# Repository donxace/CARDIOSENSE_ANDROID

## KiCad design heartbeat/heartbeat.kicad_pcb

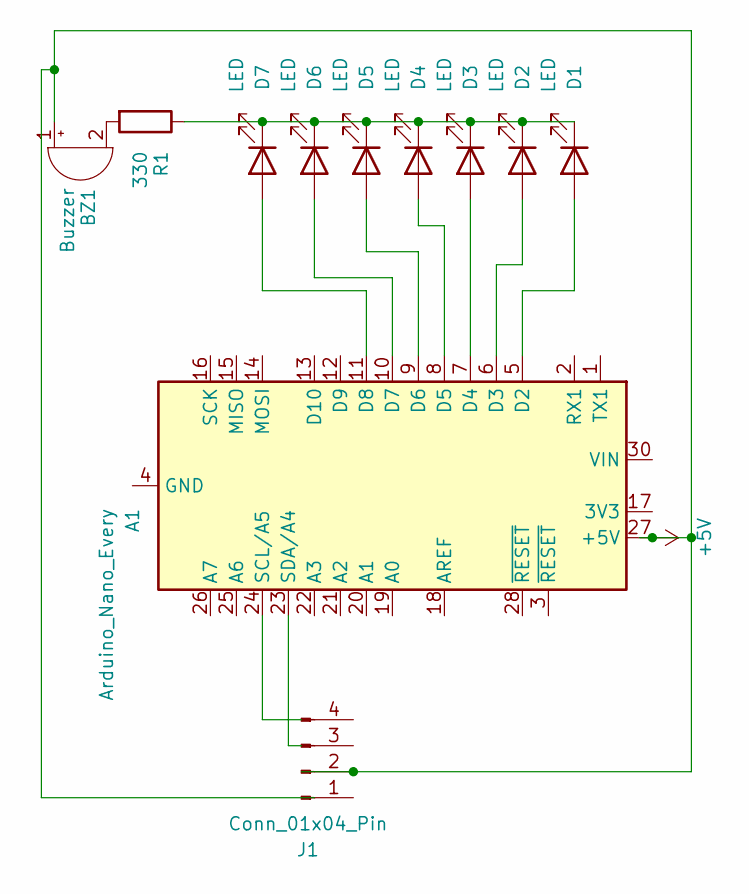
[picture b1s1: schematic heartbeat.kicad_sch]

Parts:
A1: Arduino_Nano_Every; Arduino_Nano
BZ1: Buzzer; Buzzer_15x7.5RM7.6
D1, D2, D3, D4, D5, D6, D7: LED; LED_D3.0mm
J1: Conn_01x04_Pin; PinHeader_1x04_P2.54mm_Vertical
R1: 330; R_Axial_DIN0207_L6.3mm_D2.5mm_P10.16mm_Horizontal

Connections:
+5V: A1.27 (+5V), BZ1.1 (+), J1.2
unnamed: A1.5 (D2), D1.2 (A)
unnamed: A1.6 (D3), D2.2 (A)
unnamed: A1.7 (D4), D3.2 (A)
unnamed: A1.8 (D5), D4.2 (A)
unnamed: A1.9 (D6), D5.2 (A)
unnamed: A1.10 (D7), D6.2 (A)
unnamed: A1.11 (D8), D7.2 (A)
unnamed: A1.4 (GND), A1.29 (GND)
unnamed: BZ1.2 (-), R1.2
unnamed: D1.1 (K), D2.1 (K), D3.1 (K), D4.1 (K), D5.1 (K), D6.1 (K), D7.1 (K), R1.1

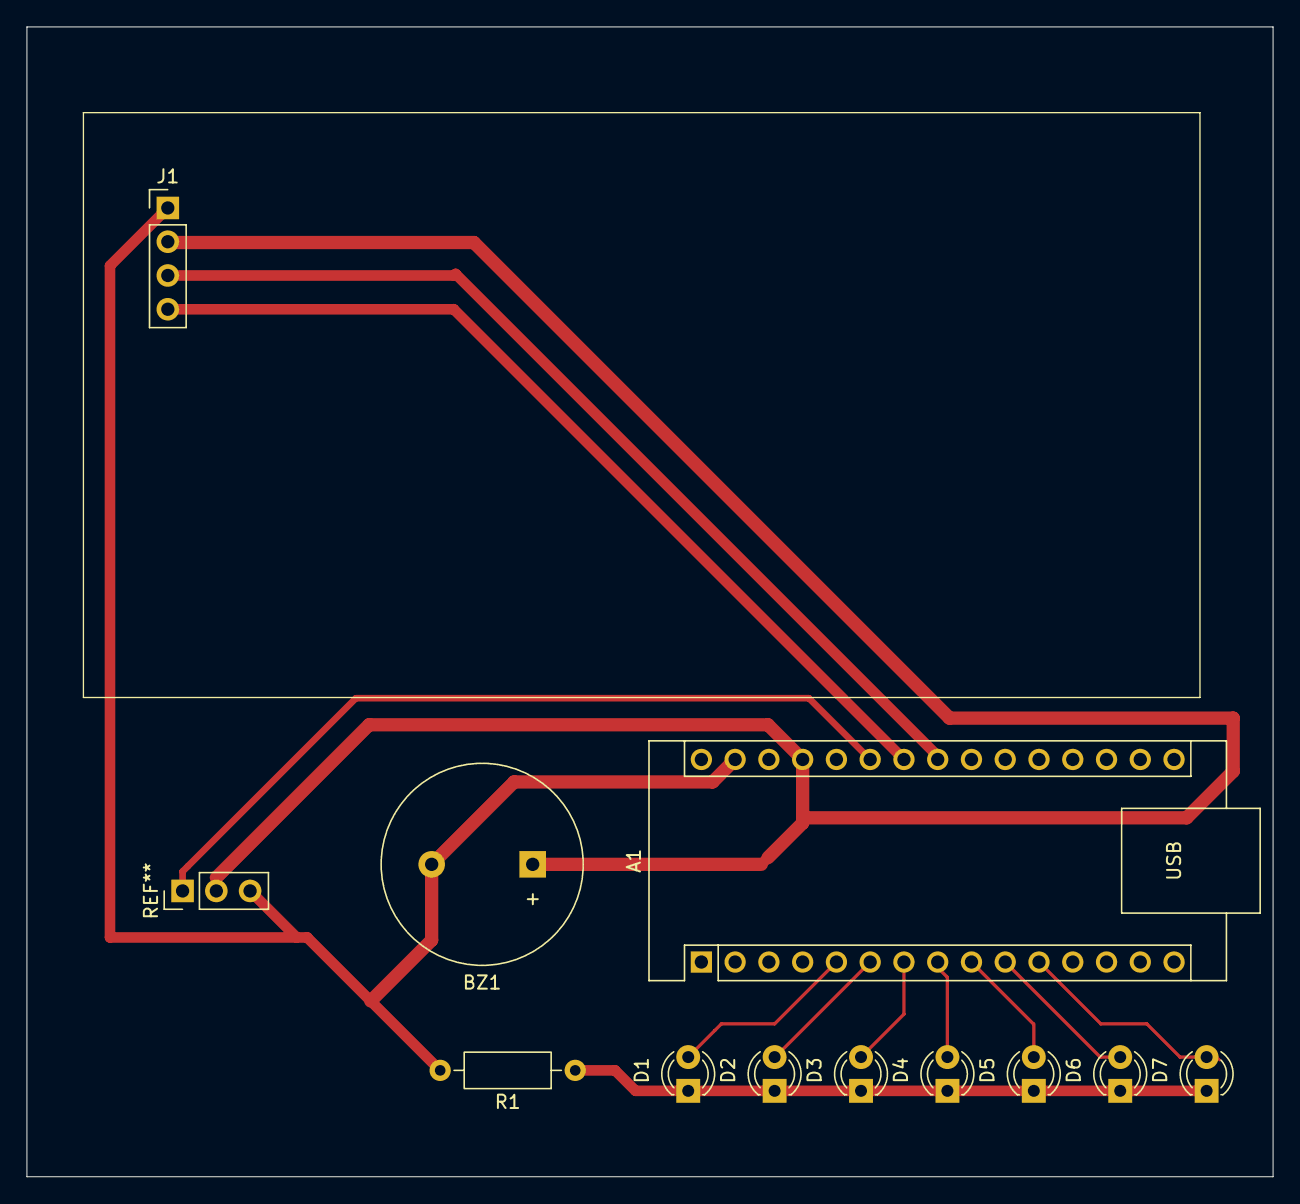
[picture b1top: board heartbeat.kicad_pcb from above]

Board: 2 copper layers, 93.8 x 86.5 mm, 11 parts (0 on the bottom side), 11 nets.

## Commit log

2025-11-06 Add SQLite Table for LSTM
2025-11-09 added new features: database, data generator, and soon BPTT. Forward pass is almost complete
2025-11-10 New Features, Hell yea
2025-11-10 added LSTM Prediction database,
    can now predict prediction values,
    created a denormalize function
2025-11-11 Added Graph Visuals
2025-11-12 no updates
2025-11-12 BPTT ADDED
2025-11-15 Did some updates on BPTT
2025-11-16 optimized BPTT
2025-11-16 Bias and Weight Update
2025-11-16 optimized a more comprehensive graph between actual data and prediction data
2025-11-23 Add files via upload
    PCB Design
2025-12-06 Initial commit: adding Android app
2025-12-14 Initial commit for CardioSense Android App
2025-12-14 Users can now login if the email and its respective password is existing in the database
2025-12-14 Added a server folder.
2025-12-14 Implement RR Interval session storage with Room database, added a stop and resume button in Time Activity + Real Time Line Graphing
2025-12-15 Fix HomeActivity graph disappearance and navigation
    - Preserve activityList in HomeViewModel to avoid disappearing graphs
    - Handle onNewIntent to update graph data when returning from other activities
    - Update buttons to use Intent flags to prevent recreating HomeActivity
    - Minor UI tweaks for ArcProgress and LineGraph
2025-12-17 Fix Room database and DAO issues, update ViewModel and Composables
    - Corrected Room entity table names to match DAO queries (SessionMetricsEntity -> session_metrics)
    - Updated SessionMetricsDao and RRIntervalDao queries to reference correct table names
    - Ensured database includes all entities in AppDatabase
    - Cleaned up Composables to properly display heart metrics and activity logs
    - Removed manual edits under build/ directory and added guidance to clean & rebuild project
2025-12-18 refactor: remove unused imports and clean up code
2025-12-18 Fix socket reconnecting and RR interval parsing
2025-12-18 Fix Room DB intergrity error
2025-12-18 Refactor HomeViewModel and ActivityLog to store and display per-activity timestamps
2025-12-19 Display BPM and average RR interval per recording for users
2025-12-19 users can now identify which part of the day(e.g., Morning Test, Afternoon Test, Evening Test)
2025-12-19 added a dynamic health score in HomeActivity
2025-12-19 Optimize health score calculation based on BPM and RMSS from ActivityRecord
2025-12-19 Updated SessionsForDayComposable and ViewModel to load RR intervals and session metrics directly from the database on composable launch.
2025-12-20 Fixes incorrect display on day and time for activity logs
2025-12-20 Improve activity records flow (patrial)
2025-12-22 Fix: Health score showing 0% on app launch
2025-12-22 Created a function that simulates activity logs based on date
2025-12-22 New Feature: Users are now enabled to browse activity records based on selected date
2025-12-22 Fix HomeActivity to display all new activity records live
2025-12-22 Created a particular file for HeartMetrics
2025-12-22 Added a refresh trigger in ViewModel to update session records and health score from TimerActivity
2025-12-24 Add time range selection in TimeDomainFeaturesScreen() to display session averages
2025-12-25 refactor: drop last30Days feature and enable lastNDays to handle future logs
2025-12-25 Add daily and weekly health score with Room and Compose integration
    - Added DailyHealthScore entity and DAO
    - Implemented suspend functions to calculate daily/weekly scores
    - Updated HomeViewModel to load health scores with viewModelScope
    - Integrated LaunchedEffect in HomeActivityScreen to update sessions and health score automatically
    - Fixed coroutine and context issues for Compose and Activity
2025-12-25 feat: display weekly health scores in Compose UI
    - Fetch daily scores and map to weekdays
    - Store in state list for Compose reactivity
    - Dynamically show Monday-Friday scores in bars
    - Enable access to individual day scores
